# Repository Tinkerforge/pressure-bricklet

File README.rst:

Pressure Bricklet
=================

**The development of this Bricklet was stopped.**

This repository contains the firmware source code and the hardware design
files. The documentation generator configs can be found at
https://github.com/Tinkerforge/generators

Repository Content
------------------

software/:
 * examples/: Examples for all supported languages
 * build/: Compiled files
 * src/: Source code of firmware
 * Makefile: Makefile to build project

hardware/:
 * Contains KiCad project files and additionally schematics as PDF

datasheets/:
 * Contains datasheets for sensors and complex ICs that are used

Hardware
--------

The hardware is designed with the open source EDA Suite KiCad
(http://www.kicad.org). Before you are able to open the files,
you have to install the Tinkerforge kicad-libraries
(https://github.com/Tinkerforge/kicad-libraries). You can either clone
them directly in hardware/ or clone them in a separate folder and
symlink them into hardware/
(ln -s kicad_path/kicad-libraries project_path/hardware). After that you
can open the .pro file in hardware/ with KiCad and from there view and
modify the schematics and the PCB layout.

Software
--------

If you want to do your own Brick/Bricklet firmware development we highly
recommend that you use our build environment setup script and read the
tutorial (https://www.tinkerforge.com/en/doc/Tutorials/Tutorial_Build_Environment/Tutorial.html).

To compile the C code we recommend you to install the newest GNU Arm Embedded
Toolchain (https://launchpad.net/gcc-arm-embedded/+download).
You also need to install bricklib (https://github.com/Tinkerforge/bricklib)
and brickletlib (https://github.com/Tinkerforge/brickletlib).

You can either clone it directly in software/src/ or clone it in a
separate folder and symlink it into software/src/
(ln -s bricklib_path/bricklib project_path/software/src/ and
ln -s brickletlib_path/brickletlib project_path/software/src/).
Finally make sure to have CMake installed
(http://www.cmake.org/cmake/resources/software.html).

After that you can build the firmware by invoking make in software/.
The firmware (.bin) can then be found in software/build/ and uploaded
with brickv (click button "Flashing" on start screen).

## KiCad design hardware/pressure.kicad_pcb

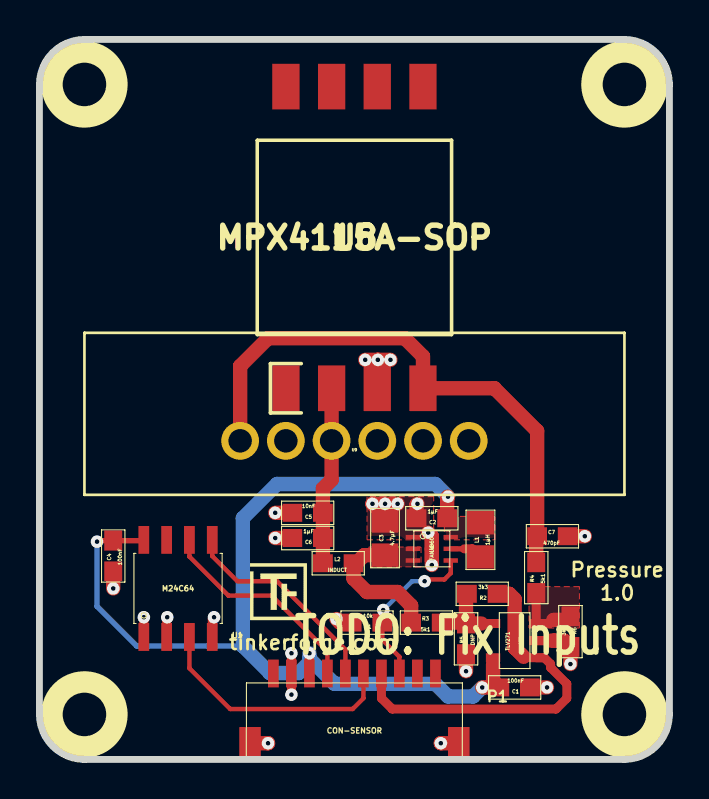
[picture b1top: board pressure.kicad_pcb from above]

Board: 2 copper layers, 35.0 x 40.0 mm, 26 parts (0 on the bottom side), 13 nets.

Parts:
C1, C4: 100nF; 0603E
C2, C6: 1µF; 0603E
C3: 4.7µF; 0805E
C5: 10nF; 0603E
C7: 470pF; 0603E
L1: 1µH; 0805E
L2: INDUCT; 0603E
P1: CON-SENSOR
R1: 10k; 0603E
R2, R6: 3k3; 0603E
R3, R4: 5k1; 0603E
R5: DNP; 0603E
U1: M24C64; SOIC8
U2, U3, U4, U5: DRILL; DRILL_NP
U6: FAN4860; UMLP_22
U7: TLV271; SOT23-5
U8: MPX4115A-SOP; SOP8
U9: MPX_UNI
VAL: CE_5mm

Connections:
3V3: C1.1, C2.2, C4.1, L1.1, P1.3, U1.8, U6.6, U7.5
+5V: C3.2, L2.1, R3.2, U6.2, U6.3
GND: C1.2, C2.1, C3.1, C4.2, C5.1, C6.1, C7.1, P1.2, P1.EP, R1.1, R5.2, R6.1, U1.1, U1.2, U1.4, U6.1, U6.EP, U7.2, U8.3, U9.2
unnamed: C5.2, C6.2, L2.2, U8.2, U9.3
unnamed: C7.2, R4.1, U8.4, U9.1
unnamed: L1.2, U6.5
unnamed: P1.6, U1.3
unnamed: P1.7, R2.2, U7.1
unnamed: P1.8, R1.2, U6.4
unnamed: R2.1, R3.1, R5.1, U7.4
unnamed: R4.2, R6.2, U7.3
SCL: P1.4, U1.6
SDA: P1.5, U1.5

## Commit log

2015-11-23 initial commit, copy files from rgb led bricklet
2015-11-23 pressure bricklet hardware prototype
2015-12-29 todo: fix input direction
2016-02-01 Add datasheets
2016-02-01 Add initial plugin version
    Calibration still missing.
2016-02-01 Add examples
2016-02-03 Add MPX4115A support
2016-02-09 Add WIP marker
2016-05-18 c: Add missing device destroy call
2016-07-01 Make the change UID comment more explicit
2017-04-13 csharp: Adapt example
2017-06-02 octave: Use javaObject instead of deprecated java_new
2017-11-30 Update examples from generator
2017-12-07 mathematica: Also generate .nb files
2018-02-02 Update examples
2018-02-19 javascript: Close div tag correctly
2018-02-20 Cleanup KiCad libraries config
    Ensure LibDir=kicad-libraries and LibName1=tinkerforge.
    Remove special library.
2018-05-24 perl: Use strict in examples
2018-06-28 Fix readme
2018-07-13 Add Makefile with docker support
2018-07-13 Update directory structure and build instructions
2018-07-13 Remove obsolete generate_makefile scripts
2018-11-06 Add rust examples
2018-11-07 rust: Accept host names for ip connection, fix naming inconsistencies
2018-11-07 rust: Rename callback receivers.
2018-12-14 Add go examples.
2018-12-14 go: Fix printf parameters.
2018-12-18 go: Change import path.
2018-12-18 go: Change import path again.
2018-12-20 rust: Reformat examples.
2019-01-24 mqtt: Add examples.
2019-01-24 mqtt: Fix example header.
2019-01-24 mqtt: Remove executable bit in example permissions.
2019-01-24 go: Minor example fixes.
2019-01-24 mqtt: Minor example fixes.
2019-03-28 mqtt: Fix whitespace.
2019-08-22 c: Adapt to bindings changes
2019-12-02 Remove examples
2019-12-02 Mark development as stopped
2020-01-13 examples: mqtt: Remove trailing whitespace.
2021-10-25 Update KiCad link
    https://www.kicad.org/blog/2021/10/Avoid-links-to-former-kicad-domain/
2022-07-06 Add license files.

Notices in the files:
hardware/pressure.kicad_pcb:
Licensed under CERN OHL v.1.1
Copyright (©) 2015, B.Nordmeyer
Copyright Tinkerforge GmbH 2015.
This documentation describes Open Hardware and is licensed under the
CERN OHL v. 1.1.
